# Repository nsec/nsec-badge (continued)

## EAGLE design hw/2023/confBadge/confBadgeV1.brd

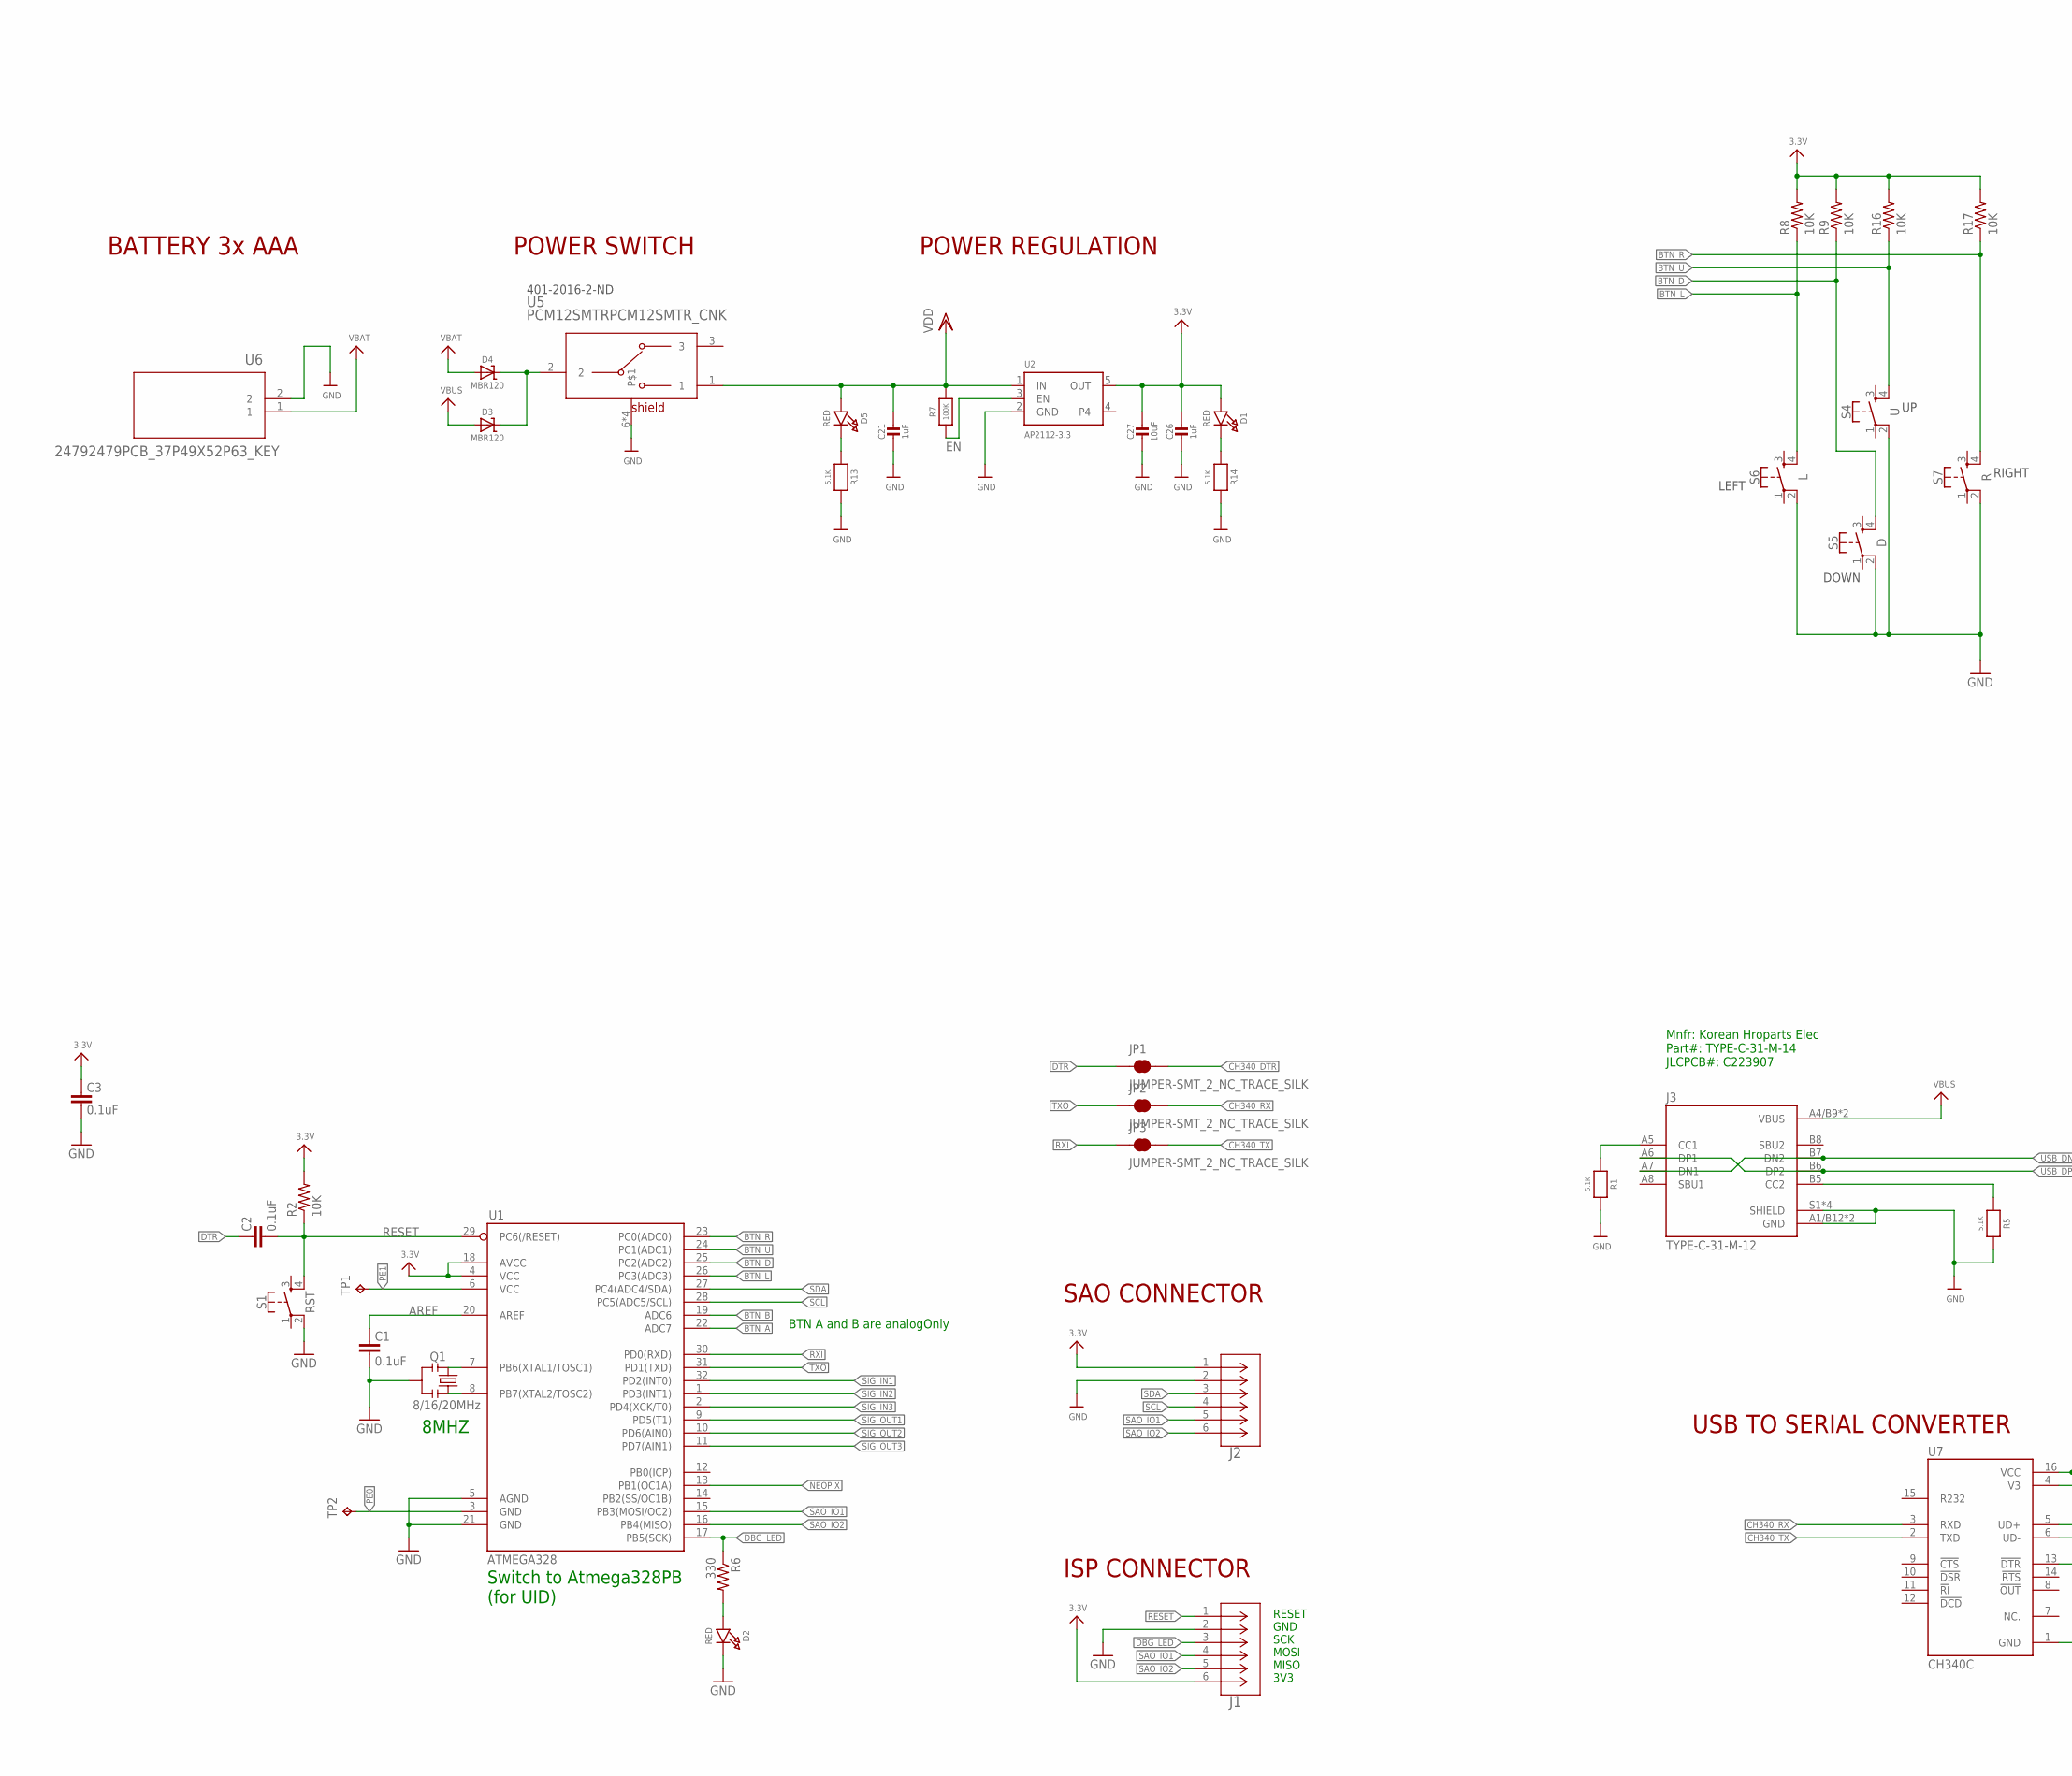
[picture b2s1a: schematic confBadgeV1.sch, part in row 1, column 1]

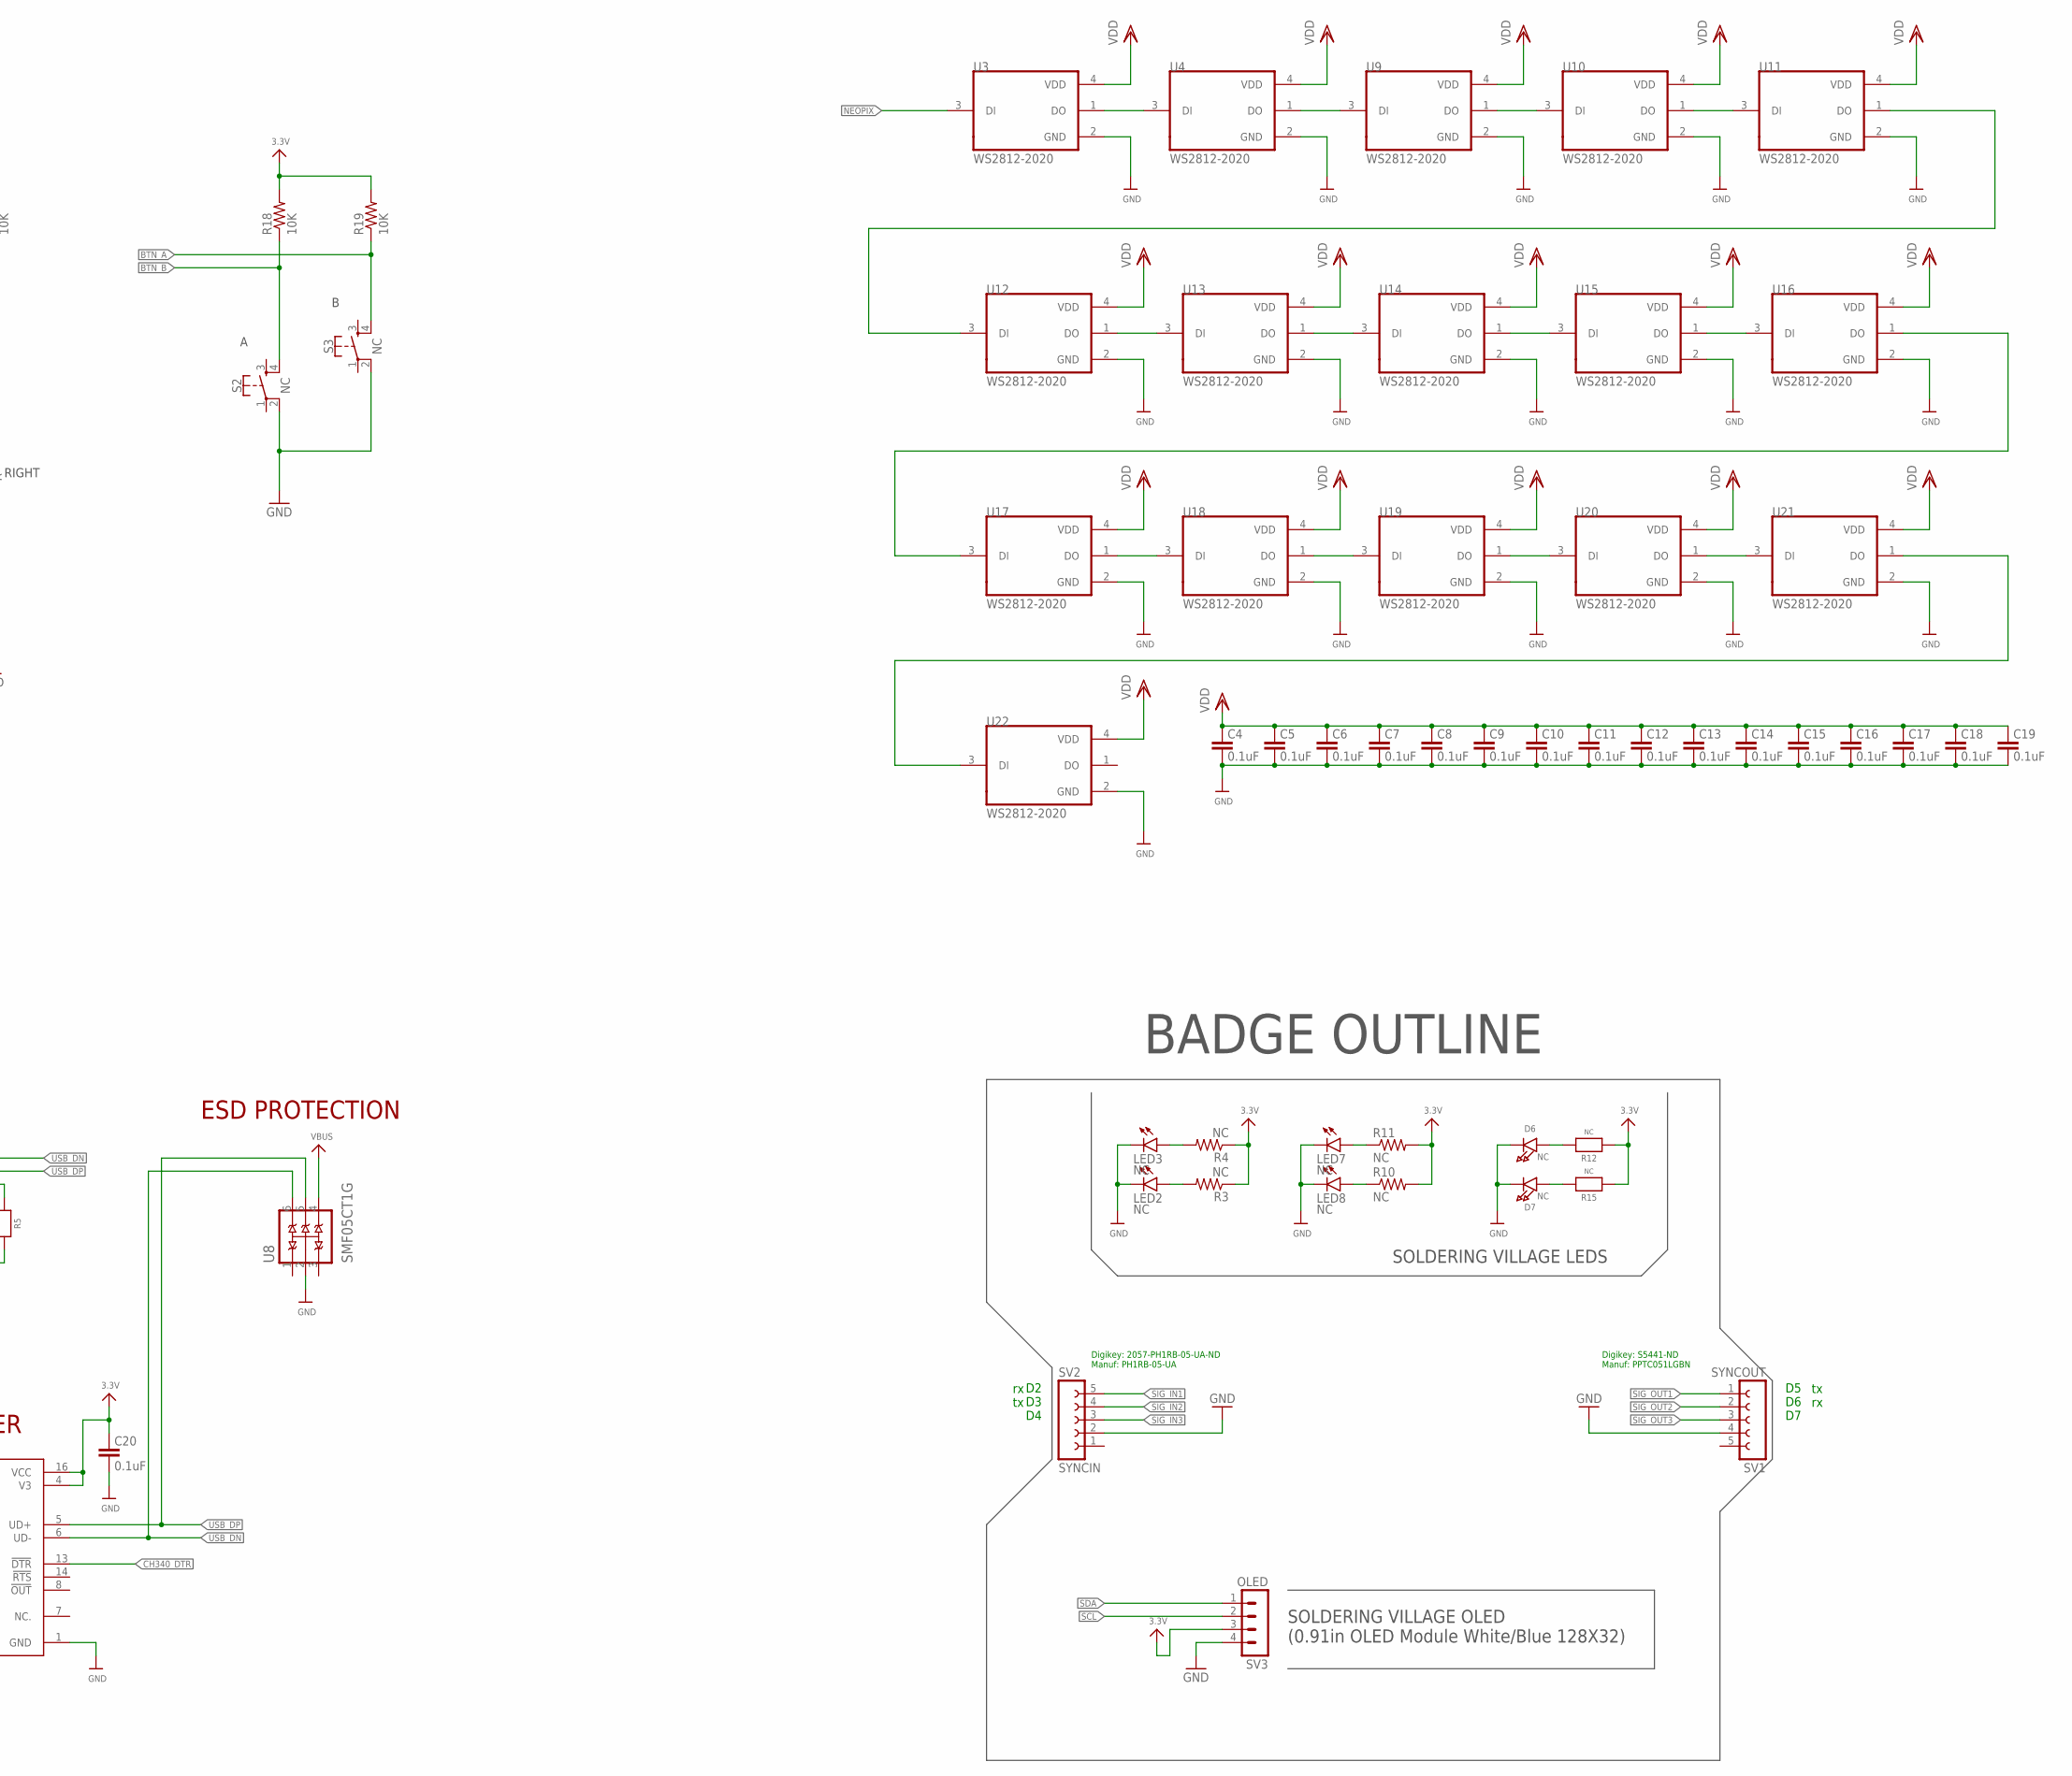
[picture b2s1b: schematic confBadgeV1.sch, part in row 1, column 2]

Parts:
C1, C2, C3, C4, C5, C6, C7, C8, C9, C10, C11, C12, C13, C14, C15, C16, C17, C18, C19, C20: 0.1uF; 0603-CAP
C21, C26: 1uF; 0603-NO
C27: 10uF; 0805-NO
D1, D2, D5: RED; CHIPLED_0805_NOOUTLINE
D3, D4: MBR120; SOD-123
D6, D7: NC; CHIPLED_0805_NOOUTLINE
J1, J2: SSW-103-22-F-D-VS-K-TRCON3_SSW-D-DUMZ_HDR_SAI; CON3_SSW-D-DUMZ_HDR_SAI
J3: TYPE-C-31-M-12; HRO_TYPE-C-31-M-12
JP1, JP2, JP3: JUMPER-SMT_2_NC_TRACE_SILK; SMT-JUMPER_2_NC_TRACE_SILK
LED2, LED3: NC; LED3MM
LED7, LED8: NC; CHIPLED_1206
Q1: 8/16/20MHz; RESONATOR-SMD-1:1
R1, R5, R13, R14: 5.1K; 0603-NO
R2, R8, R9, R16, R17, R18, R19: 10K; 0603-RES
R3, R4: NC; 0207/10
R6: 330; 0603-RES
R7: 100K; 0603-NO
R10, R11: NC; R1206W
R12, R15: NC; 0603-NO
S1: RST; TACTILE_SWITCH_SMD_5.2MM
S2, S3: NC; TACTILE_SWITCH_SMD_5.2MM
S4: U; TACTILE_SWITCH_SMD_5.2MM
S5: D; TACTILE_SWITCH_SMD_5.2MM
S6: L; TACTILE_SWITCH_SMD_5.2MM
S7: R; TACTILE_SWITCH_SMD_5.2MM
SV1: SYNCOUT; FE05W
SV2: SYNCIN; FE05W
SV3: OLED; MA04-1
TP1, TP2: TPB1,27; B1,27
U1: ATMEGA328; TQFP32-08
U2: AP2112-3.3; SOT23-5
U3, U4, U9, U10, U11, U12, U13, U14, U15, U16, U17, U18, U19, U20, U21, U22: WS2812-2020; LED_WS2812-2020
U5: PCM12SMTRPCM12SMTR_CNK; PCM12SMTR_CNK
U6: 24792479PCB_37P49X52P63_KEY; 2479PCB_37P49X52P63_KEY
U7: CH340C; SOIC127P600X180-16N
U8: SMF05CT1G; SOT65P210X110-6N

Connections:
3.3V: C3.2, C20.2, C26.1, C27.1, D1.A, J1.6, J2.1, R2.2, R3.1, R4.1, R8.2, R9.2, R10.2, R11.2, R12.1, R15.1, R16.2, R17.2, R18.2, R19.2, SV3.3, U1.4 (VCC), U1.18 (AVCC), U2.5 (OUT), U7.4 (V3), U7.16 (VCC)
AREF: C1.2, U1.20 (AREF)
BTN_A: R19.1, S3.4, U1.22 (ADC7)
BTN_B: R18.1, S2.4, U1.19 (ADC6)
BTN_D: R9.1, S5.4, U1.25 (PC2(ADC2))
BTN_L: R8.1, S6.4, U1.26 (PC3(ADC3))
BTN_R: R17.1, S7.4, U1.23 (PC0(ADC0))
BTN_U: R16.1, S4.4, U1.24 (PC1(ADC1))
CH340_DTR: JP1.2, U7.13 (!DTR)
CH340_RX: JP2.2, U7.3 (RXD)
CH340_TX: JP3.2, U7.2 (TXD)
DBG_LED: J1.3, R6.1, U1.17 (PB5(SCK))
DTR: C2.2, JP1.1
EN: R7.1, U2.3 (EN)
GND: C1.1, C3.1, C4.1, C5.1, C6.1, C7.1, C8.1, C9.1, C10.1, C11.1, C12.1, C13.1, C14.1, C15.1, C16.1, C17.1, C18.1, C19.1, C20.1, C21.2, C26.2, C27.2, D2.C, D6.C, D7.C, J1.2, J2.2, J3.A1/B12 (GND), J3.B1/A12 (GND), J3.S1 (SHIELD), J3.S2 (SHIELD), J3.S3 (SHIELD), J3.S4 (SHIELD), LED2.K (C), LED3.K (C), LED7.C, LED8.C, Q1.2, R1.2, R5.2, R13.2, R14.2, S1.2, S2.2, S3.2, S4.2, S5.2, S6.2, S7.2, SV1.4, SV2.2, SV3.4, U1.5 (AGND), U1.21 (GND), U2.2 (GND), U3.2 (GND), U4.2 (GND), U5.6, U5.7, U5.8, U5.9, U6.2, U7.1 (GND), U8.2 (A), U9.2 (GND), U10.2 (GND), U11.2 (GND), U12.2 (GND), U13.2 (GND), U14.2 (GND), U15.2 (GND), U16.2 (GND), U17.2 (GND), U18.2 (GND), U19.2 (GND), U20.2 (GND), U21.2 (GND), U22.2 (GND)
unnamed: Q1.3, U1.8 (PB7(XTAL2/TOSC2))
unnamed: Q1.1, U1.7 (PB6(XTAL1/TOSC1))
unnamed: U4.1 (DO), U9.3 (DI)
unnamed: U9.1 (DO), U10.3 (DI)
unnamed: U3.1 (DO), U4.3 (DI)
unnamed: U10.1 (DO), U11.3 (DI)
unnamed: D2.A, R6.2
unnamed: U11.1 (DO), U12.3 (DI)
unnamed: U12.1 (DO), U13.3 (DI)
unnamed: U13.1 (DO), U14.3 (DI)
unnamed: U14.1 (DO), U15.3 (DI)
unnamed: U15.1 (DO), U16.3 (DI)
unnamed: U16.1 (DO), U17.3 (DI)
unnamed: U17.1 (DO), U18.3 (DI)
unnamed: U18.1 (DO), U19.3 (DI)
unnamed: U19.1 (DO), U20.3 (DI)
unnamed: U20.1 (DO), U21.3 (DI)
unnamed: D6.A, R12.2
unnamed: LED2.A, R3.2
unnamed: U21.1 (DO), U22.3 (DI)
unnamed: LED3.A, R4.2
unnamed: D7.A, R15.2
unnamed: LED8.A, R10.1
unnamed: LED7.A, R11.1
unnamed: J3.B5 (CC2), R5.1
unnamed: J3.A5 (CC1), R1.1
unnamed: D3.C, D4.C, U5.2
unnamed: D5.C, R13.1
unnamed: D1.C, R14.1
NEOPIX: U1.13 (PB1(OC1A)), U3.3 (DI)
PE0: TP2.TP, U1.3 (GND)
PE1: TP1.TP, U1.6 (VCC)
RESET: C2.1, J1.1, R2.1, S1.4, U1.29 (PC6(/RESET))
RXI: JP3.1, U1.30 (PD0(RXD))
SAO_IO1: J1.4, J2.5, U1.15 (PB3(MOSI/OC2))
SAO_IO2: J1.5, J2.6, U1.16 (PB4(MISO))
SCL: J2.4, SV3.2, U1.28 (PC5(ADC5/SCL))
SDA: J2.3, SV3.1, U1.27 (PC4(ADC4/SDA))
SIG_IN1: SV2.5, U1.32 (PD2(INT0))
SIG_IN2: SV2.4, U1.1 (PD3(INT1))
SIG_IN3: SV2.3, U1.2 (PD4(XCK/T0))
SIG_OUT1: SV1.1, U1.9 (PD5(T1))
SIG_OUT2: SV1.2, U1.10 (PD6(AIN0))
SIG_OUT3: SV1.3, U1.11 (PD7(AIN1))
TXO: JP2.1, U1.31 (PD1(TXD))
USB_DN: J3.A7 (DN1), J3.B7 (DN2), U7.6 (UD-), U8.6 (C5)
USB_DP: J3.A6 (DP1), J3.B6 (DP2), U7.5 (UD+), U8.5 (C4)
VBAT: D4.A, U6.1
VBUS: D3.A, J3.A4/B9 (VBUS), J3.B4/A9 (VBUS), U8.4 (C3)
VDD: C4.2, C5.2, C6.2, C7.2, C8.2, C9.2, C10.2, C11.2, C12.2, C13.2, C14.2, C15.2, C16.2, C17.2, C18.2, C19.2, C21.1, D5.A, R7.2, U2.1 (IN), U3.4 (VDD), U4.4 (VDD), U5.1, U9.4 (VDD), U10.4 (VDD), U11.4 (VDD), U12.4 (VDD), U13.4 (VDD), U14.4 (VDD), U15.4 (VDD), U16.4 (VDD), U17.4 (VDD), U18.4 (VDD), U19.4 (VDD), U20.4 (VDD), U21.4 (VDD), U22.4 (VDD)

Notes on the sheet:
POWER REGULATION
401-2016-2-ND
POWER SWITCH
BATTERY 3x AAA
DOWN
LEFT
RIGHT
USB TO SERIAL CONVERTER
ESD PROTECTION
BADGE OUTLINE
SOLDERING VILLAGE OLED (0.91in OLED Module White/Blue 128X32)
SOLDERING VILLAGE LEDS
Mnfr: Korean Hroparts Elec Part#: TYPE-C-31-M-14 JLCPCB#: C223907
SAO CONNECTOR
RESET GND SCK MOSI MISO 3V3
ISP CONNECTOR
Digikey: S5441-ND Manuf: PPTC051LGBN
Digikey: 2057-PH1RB-05-UA-ND Manuf: PH1RB-05-UA
Switch to Atmega328PB (for UID)
8MHZ
D2 D3 D4
D5 D6 D7
rx tx
tx rx
BTN A and B are analogOnly

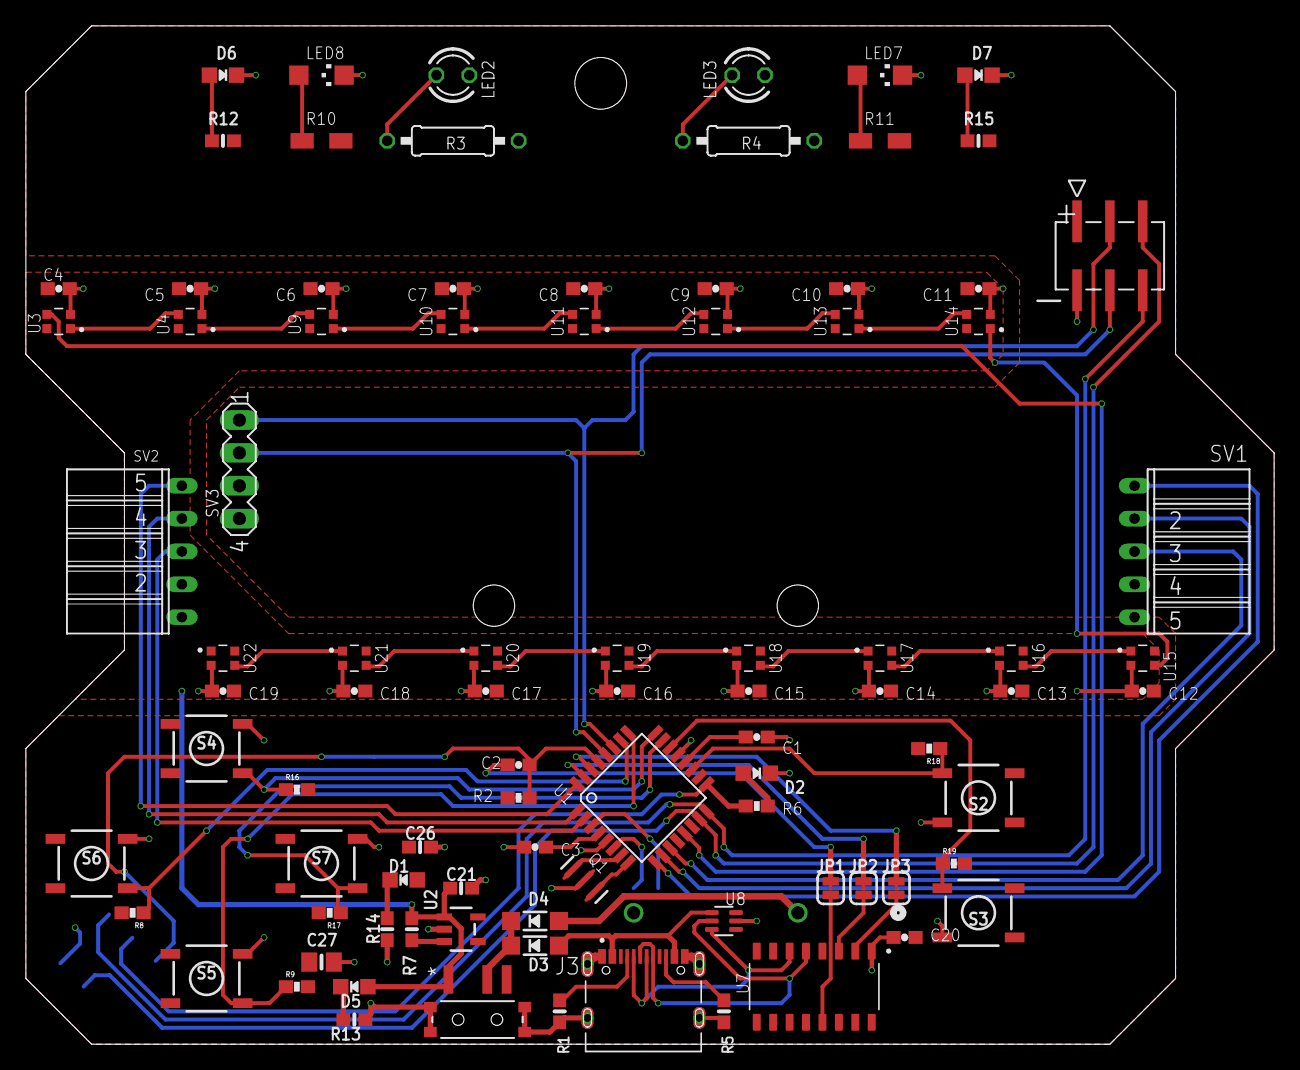
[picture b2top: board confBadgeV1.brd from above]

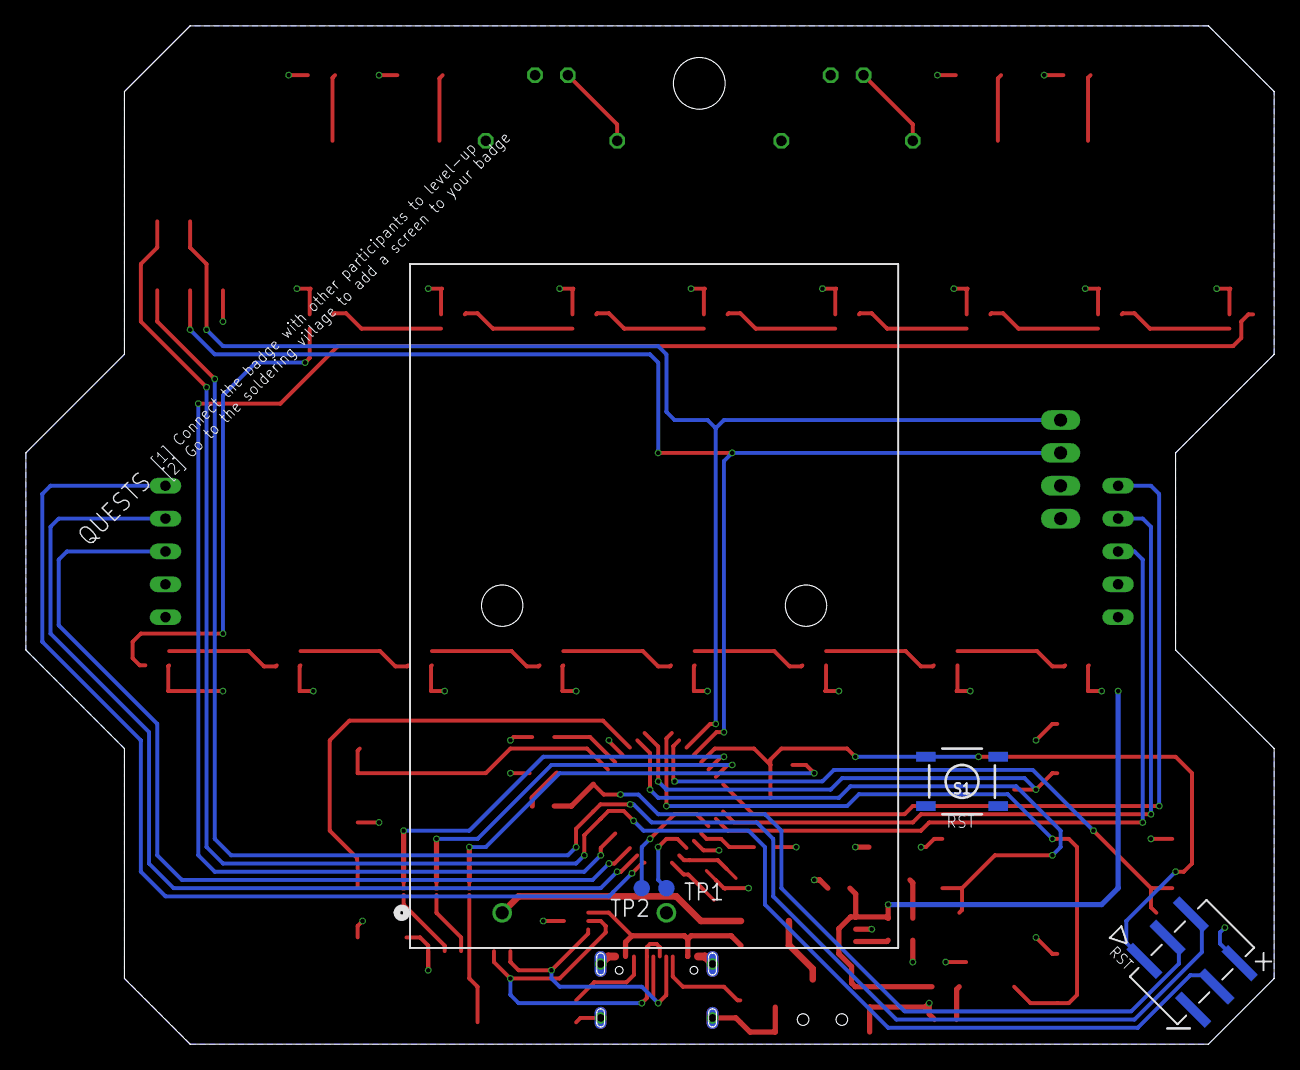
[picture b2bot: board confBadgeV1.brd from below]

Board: 2 copper layers, 96.5 x 78.7 mm, 94 parts (5 on the bottom side), 65 nets.

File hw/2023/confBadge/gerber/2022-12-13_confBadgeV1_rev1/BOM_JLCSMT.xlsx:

Comment | Designator | Footprint | JLCPCB | DIGIKEY
0.1uF | C1, C2, C3, C4, C5, C6, C7, C8, C9, C10, C11, C12, C13, C14, C15, C16, C17, C18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 | 0603-CAP | C14663
100K | R7 | 0603-NO | C25803
10K | R2, R8, R9, R16, R17, R18, R19 | 0603-RES | C25804
10uF | C27 | 0805-NO | C440198
1uF | C21, C26 | 0603-NO | C15849
24792479PCB_37P49X52P63_KEY | U6 | 2479PCB_37P49X52P63_KEY |  | 36-2479-ND
330 | R6 | 0603-RES | C23138
5.1K | R1, R5, R13, R14 | 0603-NO | C23186
8/16/20MHz | Q1 | RESONATOR-SMD-1:1 | C22549
AP2112-3.3 | U2 | SOT23-5 | C150742
ATMEGA328PB-AU | U1 | TQFP32-08 | C132230
CH340C | U7 | SOIC127P600X180-16N | C84681
Button | S6, S2, S3, S5, S7, S4 | TACTILE_SWITCH_SMD_5.2MM | C318884
MBR120 | D3, D4 | SOD-123 | C130880
NC | D6, D7 | CHIPLED_0805_NOOUTLINE |  |  | not connected
NC | LED2, LED3 | LED3MM |  |  | not connected
NC | LED7, LED8 | CHIPLED_1206 |  |  | not connected
NC | R3, R4 | 0207/10 |  |  | not connected
NC | R10, R11 | R1206W |  |  | not connected
NC | R12, R15 | 0603-NO |  |  | not connected
OLED | SV3 | MA04-1 |  |  | not connected
PCM12SMTRPCM12SMTR_CNK | U5 | PCM12SMTR_CNK |  | 401-2016-2-ND
RED | D1, D2, D5 | CHIPLED_0805_NOOUTLINE | C84256
RST | S1 | TACTILE_SWITCH_SMD_5.2MM |  |  | not connected
SMF05CT1G | U8 | SOT65P210X110-6N | C558443
SSW-103-22-F-D-VS-K-TRCON3_SSW-D-DUMZ_HDR_SAI | J1, J2 | CON3_SSW-D-DUMZ_HDR_SAI |  | SAM14622TR-ND
SYNCIN | SV2 | FE05W |  | 2057-PH1RB-05-UA-ND
SYNCOUT | SV1 | FE05W |  | S5441-ND
TYPE-C-31-M-12 | J3 | HRO_TYPE-C-31-M-12 | C165948
WS2812-2020 | U3, U4, U9, U10, U11, U12, U13, U14, U15, U16, U17, U18, U19, U20, U21, U22 | LED_WS2812-2020 | C965555

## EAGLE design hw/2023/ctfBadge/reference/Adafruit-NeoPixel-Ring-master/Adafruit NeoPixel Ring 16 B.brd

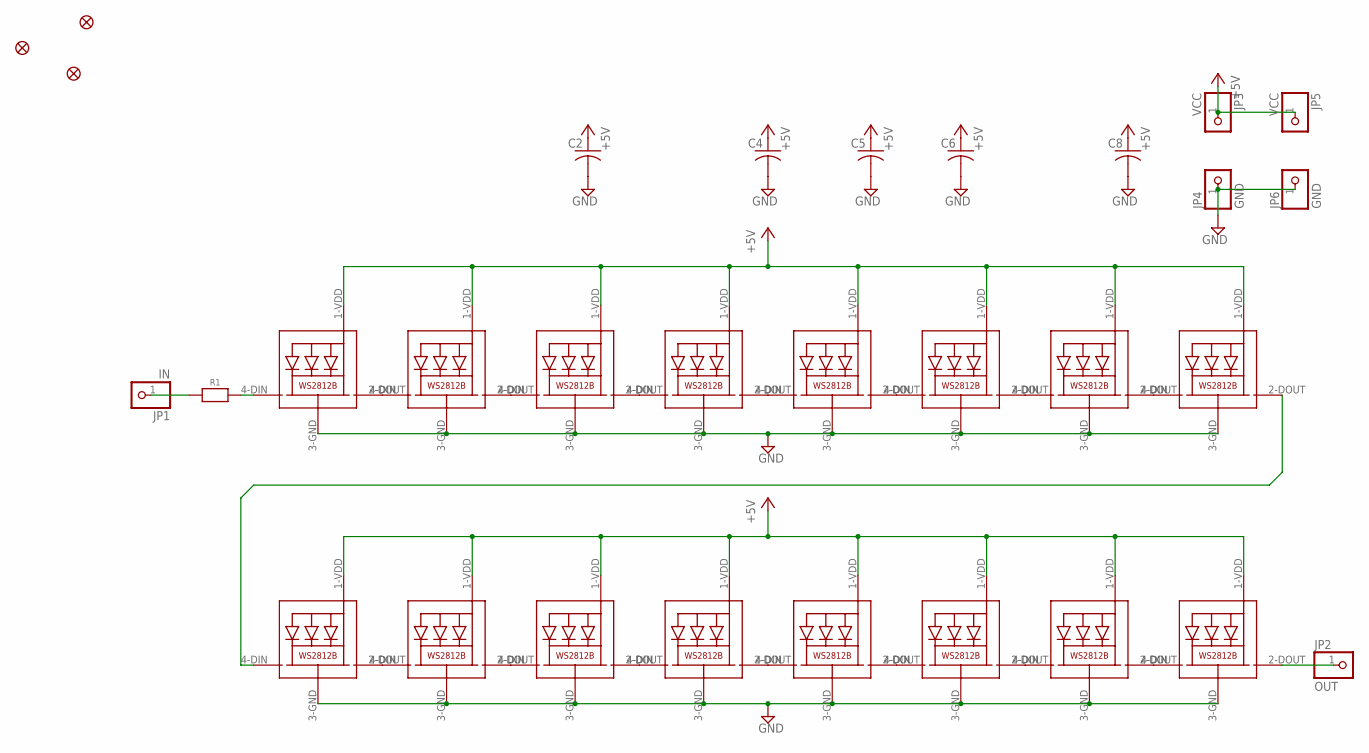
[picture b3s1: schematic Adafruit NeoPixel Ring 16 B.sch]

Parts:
C2, C4, C5, C6, C8: C-USC0603K; C0603K
FID1, FID2, FID3: FIDUCIAL""; FIDUCIAL_1MM
JP1: IN; 1X01-CLEANBIG
JP2: OUT; 1X01-CLEANBIG
JP3, JP5: VCC; 1X01-CLEANBIG
JP4, JP6: GND; 1X01-CLEANBIG
LED1, LED2, LED3, LED4, LED5, LED6, LED7, LED8, LED9, LED10, LED11, LED12, LED13, LED14, LED15, LED16: WS2812B5050; WS2812B
R1: RESISTOR_0603_NOOUT; 0603-NO

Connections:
+5V: C2.1, C4.1, C5.1, C6.1, C8.1, JP3.1, JP5.1, LED1.1-VDD (VDD), LED2.1-VDD (VDD), LED3.1-VDD (VDD), LED4.1-VDD (VDD), LED5.1-VDD (VDD), LED6.1-VDD (VDD), LED7.1-VDD (VDD), LED8.1-VDD (VDD), LED9.1-VDD (VDD), LED10.1-VDD (VDD), LED11.1-VDD (VDD), LED12.1-VDD (VDD), LED13.1-VDD (VDD), LED14.1-VDD (VDD), LED15.1-VDD (VDD), LED16.1-VDD (VDD)
GND: C2.2, C4.2, C5.2, C6.2, C8.2, JP4.1, JP6.1, LED1.3-GND (GND), LED2.3-GND (GND), LED3.3-GND (GND), LED4.3-GND (GND), LED5.3-GND (GND), LED6.3-GND (GND), LED7.3-GND (GND), LED8.3-GND (GND), LED9.3-GND (GND), LED10.3-GND (GND), LED11.3-GND (GND), LED12.3-GND (GND), LED13.3-GND (GND), LED14.3-GND (GND), LED15.3-GND (GND), LED16.3-GND (GND)
IN: JP1.1, R1.1
unnamed: LED1.2-DOUT (DO), LED2.4-DIN (DI)
unnamed: LED2.2-DOUT (DO), LED3.4-DIN (DI)
unnamed: LED3.2-DOUT (DO), LED4.4-DIN (DI)
unnamed: LED4.2-DOUT (DO), LED5.4-DIN (DI)
unnamed: LED5.2-DOUT (DO), LED6.4-DIN (DI)
unnamed: LED6.2-DOUT (DO), LED7.4-DIN (DI)
unnamed: LED7.2-DOUT (DO), LED8.4-DIN (DI)
unnamed: LED1.4-DIN (DI), R1.2
unnamed: LED9.2-DOUT (DO), LED10.4-DIN (DI)
unnamed: LED10.2-DOUT (DO), LED11.4-DIN (DI)
unnamed: LED11.2-DOUT (DO), LED12.4-DIN (DI)
unnamed: LED12.2-DOUT (DO), LED13.4-DIN (DI)
unnamed: LED13.2-DOUT (DO), LED14.4-DIN (DI)
unnamed: LED14.2-DOUT (DO), LED15.4-DIN (DI)
unnamed: LED15.2-DOUT (DO), LED16.4-DIN (DI)
unnamed: LED8.2-DOUT (DO), LED9.4-DIN (DI)
OUT: JP2.1, LED16.2-DOUT (DO)

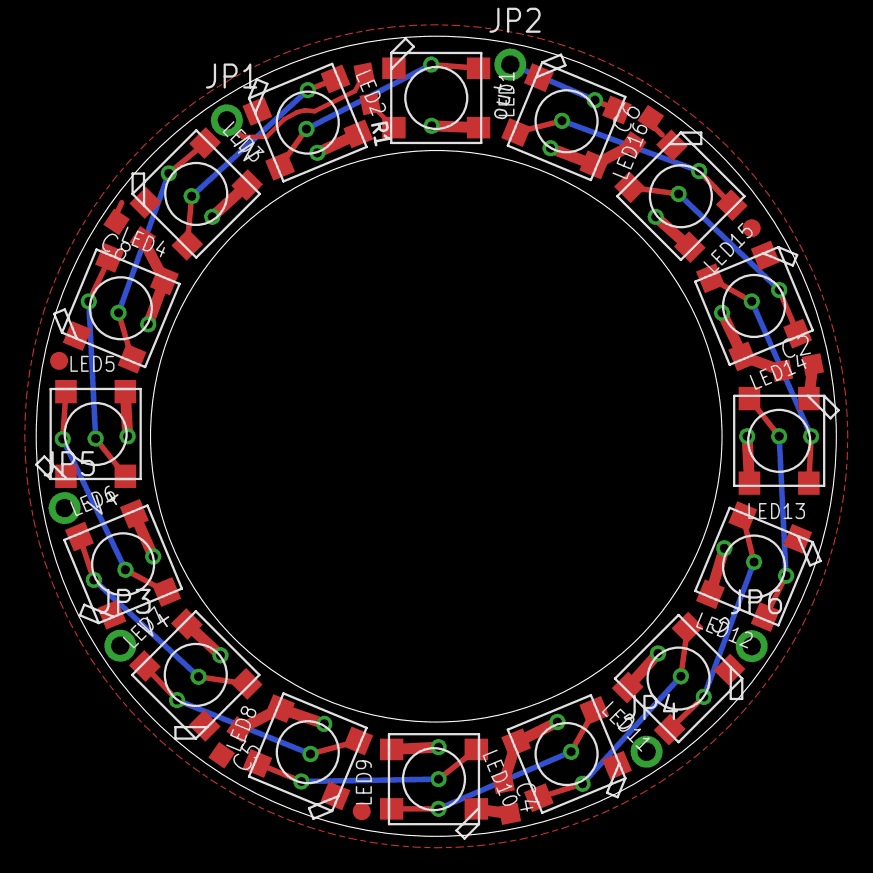
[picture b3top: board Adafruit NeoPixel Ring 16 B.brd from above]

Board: 2 copper layers, 44.5 x 44.5 mm, 32 parts (1 on the bottom side), 20 nets.

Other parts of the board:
U$2: ADAFRUIT_5MM

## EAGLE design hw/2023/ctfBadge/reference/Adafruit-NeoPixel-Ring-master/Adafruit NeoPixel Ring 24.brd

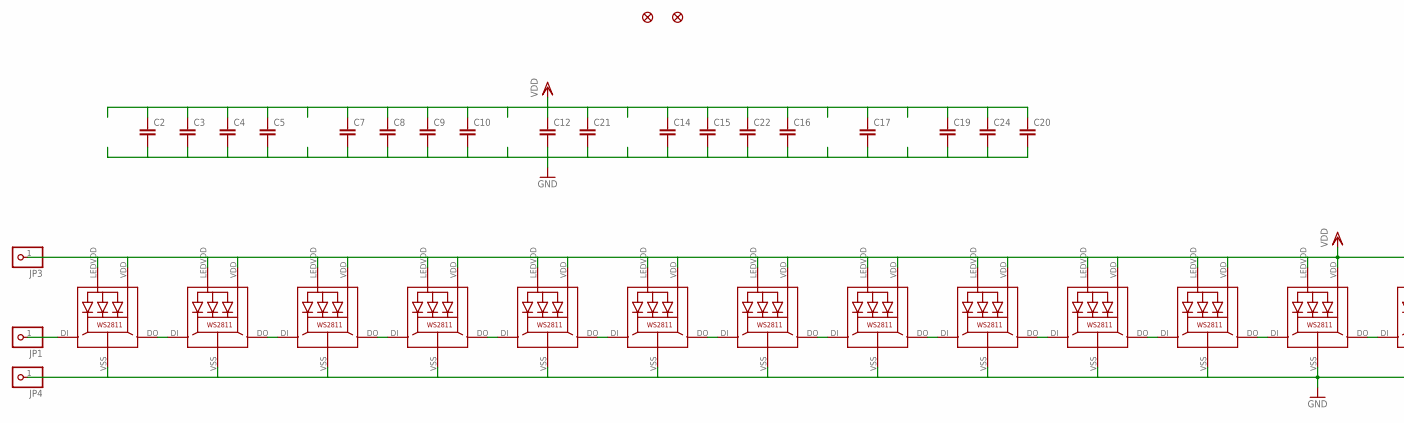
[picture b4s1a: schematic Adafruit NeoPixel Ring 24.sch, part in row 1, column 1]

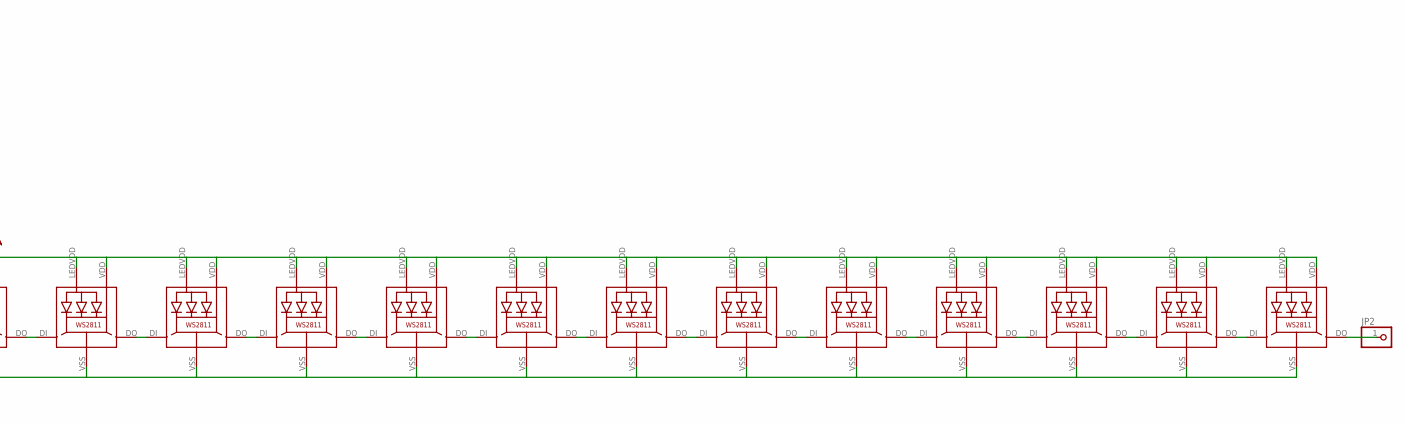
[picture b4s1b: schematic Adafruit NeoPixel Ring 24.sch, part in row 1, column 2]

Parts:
C2, C3, C4, C5, C7, C8, C9, C10, C12, C14, C15, C16, C17, C19, C20, C21, C22, C24: C-EUC0603; C0603
FID1, FID2: FIDUCIAL""; FIDUCIAL_1MM
JP1, JP2, JP3, JP4: PINHD-1X1CB; 1X01-CLEANBIG
LED1, LED2, LED3, LED4, LED5, LED6, LED7, LED8, LED9, LED10, LED11, LED12, LED13, LED14, LED15, LED16, LED17, LED18, LED19, LED20, LED21, LED22, LED23, LED24: WS28115050

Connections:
GND: C2.2, C3.2, C4.2, C5.2, C7.2, C8.2, C9.2, C10.2, C12.2, C14.2, C15.2, C16.2, C17.2, C19.2, C20.2, C21.2, C22.2, C24.2, JP4.1, LED1.VSS (GND), LED2.VSS (GND), LED3.VSS (GND), LED4.VSS (GND), LED5.VSS (GND), LED6.VSS (GND), LED7.VSS (GND), LED8.VSS (GND), LED9.VSS (GND), LED10.VSS (GND), LED11.VSS (GND), LED12.VSS (GND), LED13.VSS (GND), LED14.VSS (GND), LED15.VSS (GND), LED16.VSS (GND), LED17.VSS (GND), LED18.VSS (GND), LED19.VSS (GND), LED20.VSS (GND), LED21.VSS (GND), LED22.VSS (GND), LED23.VSS (GND), LED24.VSS (GND)
unnamed: LED1.DO, LED2.DI
unnamed: LED2.DO, LED3.DI
unnamed: LED3.DO, LED4.DI
unnamed: LED4.DO, LED5.DI
unnamed: LED5.DO, LED6.DI
unnamed: LED6.DO, LED7.DI
unnamed: LED7.DO, LED8.DI
unnamed: LED8.DO, LED9.DI
unnamed: LED9.DO, LED10.DI
unnamed: LED10.DO, LED11.DI
unnamed: LED11.DO, LED12.DI
unnamed: LED12.DO, LED13.DI
unnamed: LED13.DO, LED14.DI
unnamed: LED14.DO, LED15.DI
unnamed: LED15.DO, LED16.DI
unnamed: LED16.DO, LED17.DI
unnamed: LED17.DO, LED18.DI
unnamed: LED18.DO, LED19.DI
unnamed: LED19.DO, LED20.DI
unnamed: LED20.DO, LED21.DI
unnamed: LED21.DO, LED22.DI
unnamed: LED22.DO, LED23.DI
unnamed: LED23.DO, LED24.DI
unnamed: JP2.1, LED24.DO
unnamed: JP1.1, LED1.DI
VDD: C2.1, C3.1, C4.1, C5.1, C7.1, C8.1, C9.1, C10.1, C12.1, C14.1, C15.1, C16.1, C17.1, C19.1, C20.1, C21.1, C22.1, C24.1, JP3.1, LED1.LEDVDD, LED1.VDD, LED2.LEDVDD, LED2.VDD, LED3.LEDVDD, LED3.VDD, LED4.LEDVDD, LED4.VDD, LED5.LEDVDD, LED5.VDD, LED6.LEDVDD, LED6.VDD, LED7.LEDVDD, LED7.VDD, LED8.LEDVDD, LED8.VDD, LED9.LEDVDD, LED9.VDD, LED10.LEDVDD, LED10.VDD, LED11.LEDVDD, LED11.VDD, LED12.LEDVDD, LED12.VDD, LED13.LEDVDD, LED13.VDD, LED14.LEDVDD, LED14.VDD, LED15.LEDVDD, LED15.VDD, LED16.LEDVDD, LED16.VDD, LED17.LEDVDD, LED17.VDD, LED18.LEDVDD, LED18.VDD, LED19.LEDVDD, LED19.VDD, LED20.LEDVDD, LED20.VDD, LED21.LEDVDD, LED21.VDD, LED22.LEDVDD, LED22.VDD, LED23.LEDVDD, LED23.VDD, LED24.LEDVDD, LED24.VDD

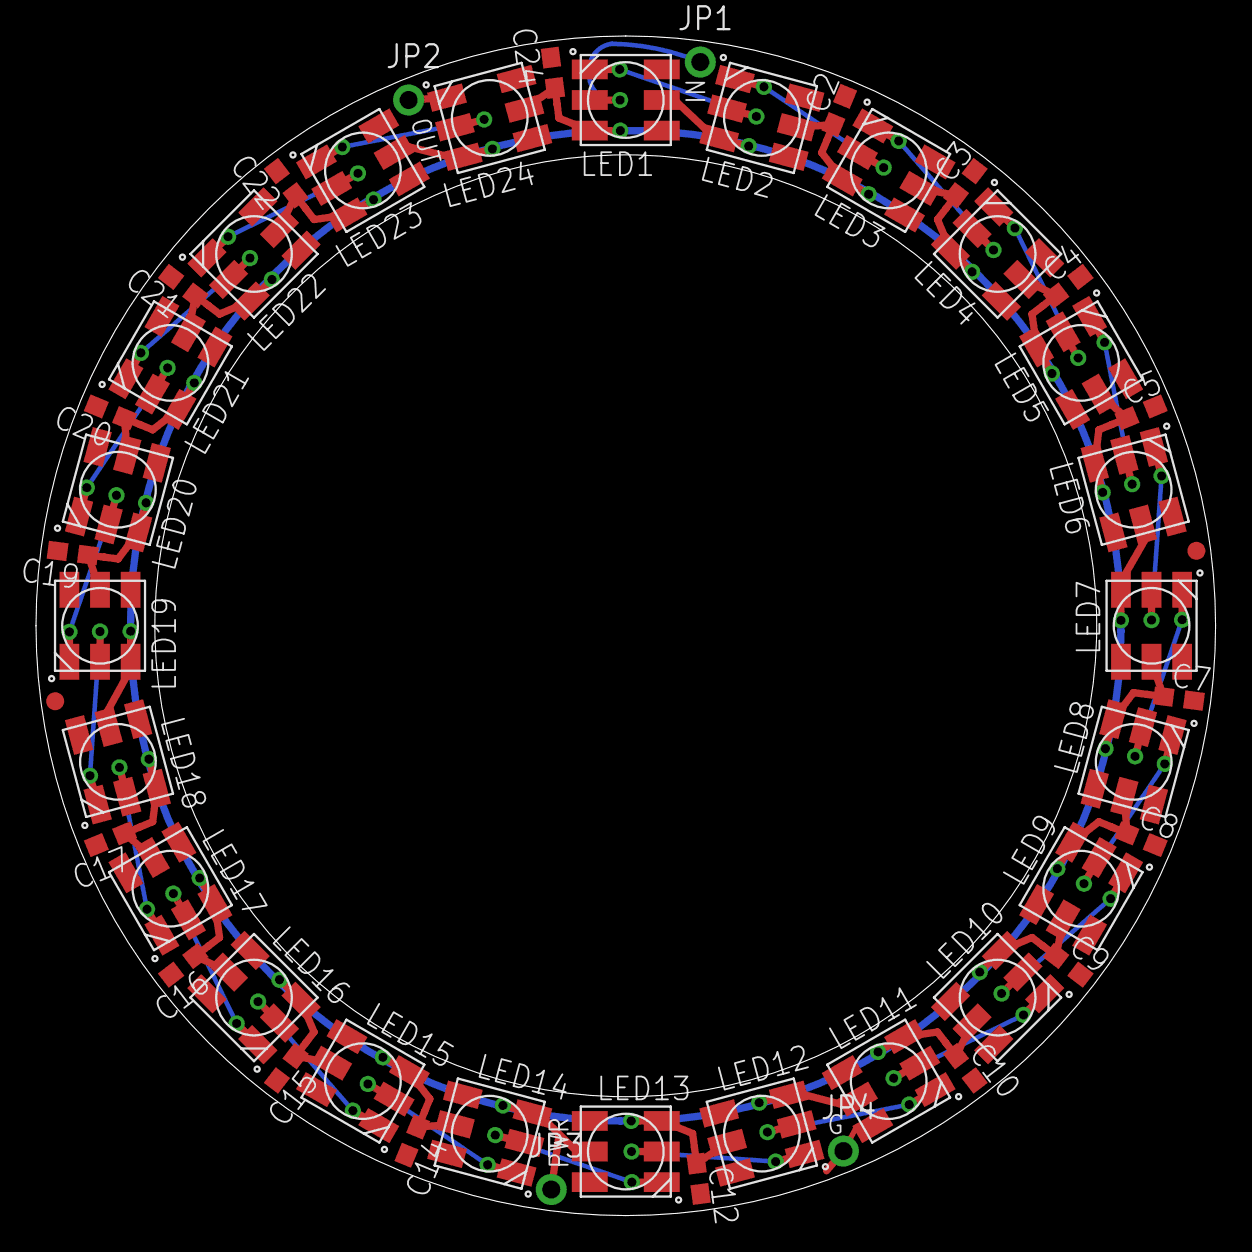
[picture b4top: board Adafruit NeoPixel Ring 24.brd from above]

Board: 2 copper layers, 65.5 x 65.5 mm, 49 parts (1 on the bottom side), 27 nets.

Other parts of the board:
U$1: ADAFRUIT_5MM
